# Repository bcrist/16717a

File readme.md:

# 16717A Logic Analyzer Redux

The HP/Agilent 16700A/B and 16702A/B logic analyzer mainframes were originally released somewhere between 1998 and 1999, and though they have now been obsolete for many years, they can still be useful for hobbyists who need to debug digital circuits with large parallel buses (especially the homebrew CPU community, who build computers from scratch, often using nothing but 7400-series logic and parallel SRAM chips).  These "boat anchors" were the last logic analyzers produced which do not use commodity PC hardware or run Windows; instead they run HP's unix variant (HP-UX) on a 150MHz PA-RISC processor.  All the operating system and analysis software is still available, and can be run from a SCSI hard drive emulator like SCSI2SD or ZuluSCSI.  And since it is just an X-windows application, you can run an X server on a modern machine with a high resolution monitor and then view the analysis software on that instead of being limited to the built-in 1024x768 LCD.

The actual triggering, sampling, and storage of waveform data is done on up to five modules.  HP/Agilent produced a variety of these, but the ones most commonly found today are:
* 16710A, 16711A, 16712A: up to 128k sample depth, 104 channels (max. 208 with 2 modules), 100MHz state analysis, 500MHz timing analysis
* 16715A, 16716A, 16717A: up to 4M sample depth, 68 channels (max. 340 with 5 modules), 333MHz state analysis, 2GHz timing analysis (except 16715A)

There's only two different PCBs used for these and the lower model numbers are effectively just software limited to a lower memory depth and can be "upgraded" by adding or removing a resistor (apart from the 16715A which lacks all the timing zoom chips).

All the 167xxA modules had plastic sliders on the bottom to prevent damage to any components on that side if not installed carefully.  Unfortunately, these rails were attached with a foam/rubber adhesive that over time either becomes corrosive, or absorbs water from the air which then becomes corrosive.  This has been documented extensively on the [EEVblog forums](https://www.eevblog.com/forum/repair/series-defect-on-agilent-167xx-boards/).  It seems this corrosion begins to appear pretty reliably around 5 years after the board was made.  As of 2025, any board which has not already had the rails removed is almost guaranteed to no longer be fully functional.  Depending on the damage, it may still be possible to repair, but if any corrosion managed to work its way into a via connecting to one of the internal signal layers, it will likely be unfixable.  I have a handful of 16717A boards like this, and multi-layer PCBs have become surprisingly affordable in recent years, so I decided to desolder all the components from one and sand down the PCB layer by layer to reverse engineer it.  You can find the scans from this in the [scans](./scans/) directory.

# Reference Design
In the [original](./original/) directory you can find my reverse-engineered version of the 16717A that is as close to the original board design as I could make it based on my scans.  Due to distortion, there may be some errors in component and trace placement, however it includes all test points from the original and should be useful when debugging failed 16717A boards.  Unfortunately there are a number of signals that I can't confidently guess at their purpose, so I just named them things like `CTRL1` etc.

# Redux Design
I wasn't happy with a number of things about the original design, so I decided to create a modified version that I think should be more reliable, and if you're going to have these boards made, it's the one I would suggest.  This version is pictured above, and the details can be found in the [redux](./redux) directory.  As of this writing, ordering a set of 5 PCBs from JLCPCB will cost between $260 - $310 depending on solder mask color and shipping selections.

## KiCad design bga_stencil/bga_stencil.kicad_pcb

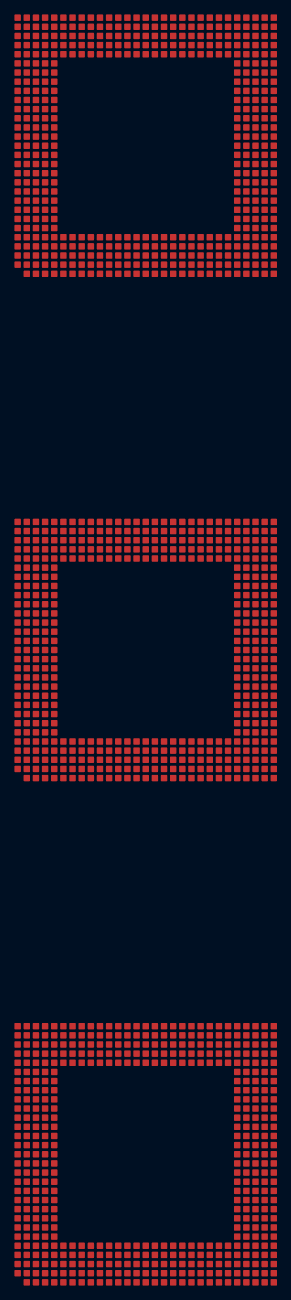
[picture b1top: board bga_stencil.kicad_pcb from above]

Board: 2 copper layers, 3 parts (0 on the bottom side), 2 nets, no tracks yet.

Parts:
U1, U2, U3: 1821-3936; BGA-479_40.5mm_P1.27mm_Stencil

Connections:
+3.3V: U1.A3 (+3.3V), U1.A5 (+3.3V), U1.A10 (+3.3V), U1.A11 (+3.3V), U1.A14 (+3.3V), U1.A16 (+3.3V), U1.A19 (+3.3V), U1.A20 (+3.3V), U1.A27 (+3.3V), U1.A29 (+3.3V), U1.AA1 (+3.3V), U1.AB3 (+3.3V), U1.AB29 (+3.3V), U1.AC1 (+3.3V), U1.AC3 (+3.3V), U1.AC5 (+3.3V), U1.AC10 (+3.3V), U1.AC11 (+3.3V), U1.AC14 (+3.3V), U1.AC16 (+3.3V), U1.AC19 (+3.3V), U1.AC20 (+3.3V), U1.AC27 (+3.3V), U1.AC29 (+3.3V), U1.B2 (+3.3V), U1.C1 (+3.3V), U1.C29 (+3.3V), U1.J1 (+3.3V), U1.J29 (+3.3V), U1.K1 (+3.3V), U1.K29 (+3.3V), U1.N1 (+3.3V), U1.N29 (+3.3V), U1.P1 (+3.3V), U1.R29 (+3.3V), U1.S1 (+3.3V), U1.S29 (+3.3V), U1.T1 (+3.3V), U1.T29 (+3.3V), U1.W29 (+3.3V), U2.A3 (+3.3V), U2.A5 (+3.3V), U2.A10 (+3.3V), U2.A11 (+3.3V), U2.A14 (+3.3V), U2.A16 (+3.3V), U2.A19 (+3.3V), U2.A20 (+3.3V), U2.A27 (+3.3V), U2.A29 (+3.3V), U2.AA1 (+3.3V), U2.AB3 (+3.3V), U2.AB29 (+3.3V), U2.AC1 (+3.3V), U2.AC3 (+3.3V), U2.AC5 (+3.3V), U2.AC10 (+3.3V), U2.AC11 (+3.3V), U2.AC14 (+3.3V), U2.AC16 (+3.3V), U2.AC19 (+3.3V), U2.AC20 (+3.3V), U2.AC27 (+3.3V), U2.AC29 (+3.3V), U2.B2 (+3.3V), U2.C1 (+3.3V), U2.C29 (+3.3V), U2.J1 (+3.3V), U2.J29 (+3.3V), U2.K1 (+3.3V), U2.K29 (+3.3V), U2.N1 (+3.3V), U2.N29 (+3.3V), U2.P1 (+3.3V), U2.R29 (+3.3V), U2.S1 (+3.3V), U2.S29 (+3.3V), U2.T1 (+3.3V), U2.T29 (+3.3V), U2.W29 (+3.3V), U3.A3 (+3.3V), U3.A5 (+3.3V), U3.A10 (+3.3V), U3.A11 (+3.3V), U3.A14 (+3.3V), U3.A16 (+3.3V), U3.A19 (+3.3V), U3.A20 (+3.3V), U3.A27 (+3.3V), U3.A29 (+3.3V), U3.AA1 (+3.3V), U3.AB3 (+3.3V), U3.AB29 (+3.3V), U3.AC1 (+3.3V), U3.AC3 (+3.3V), U3.AC5 (+3.3V), U3.AC10 (+3.3V), U3.AC11 (+3.3V), U3.AC14 (+3.3V), U3.AC16 (+3.3V), U3.AC19 (+3.3V), U3.AC20 (+3.3V), U3.AC27 (+3.3V), U3.AC29 (+3.3V), U3.B2 (+3.3V), U3.C1 (+3.3V), U3.C29 (+3.3V), U3.J1 (+3.3V), U3.J29 (+3.3V), U3.K1 (+3.3V), U3.K29 (+3.3V), U3.N1 (+3.3V), U3.N29 (+3.3V), U3.P1 (+3.3V), U3.R29 (+3.3V), U3.S1 (+3.3V), U3.S29 (+3.3V), U3.T1 (+3.3V), U3.T29 (+3.3V), U3.W29 (+3.3V)
GND: U1.A2 (GND), U1.A4 (GND), U1.A7 (GND), U1.A8 (GND), U1.A9 (GND), U1.A12 (GND), U1.A15 (GND), U1.A18 (GND), U1.A21 (GND), U1.A22 (GND), U1.A23 (GND), U1.A25 (GND), U1.A26 (GND), U1.A28 (GND), U1.AA29 (GND), U1.AB1 (GND), U1.AB2 (GND), U1.AB28 (GND), U1.AC2 (GND), U1.AC4 (GND), U1.AC7 (GND), U1.AC8 (GND), U1.AC9 (GND), U1.AC12 (GND), U1.AC15 (GND), U1.AC18 (GND), U1.AC21 (GND), U1.AC22 (GND), U1.AC23 (GND), U1.AC25 (GND), U1.AC26 (GND), U1.AC28 (GND), U1.B1 (GND), U1.B29 (GND), U1.D1 (GND), U1.D29 (GND), U1.E1 (GND), U1.E29 (GND), U1.G1 (GND), U1.G29 (GND), U1.H1 (GND), U1.H29 (GND), U1.I1 (GND), U1.I29 (GND), U1.L1 (GND), U1.L29 (GND), U1.O1 (GND), U1.O29 (GND), U1.P29 (GND), U1.R1 (GND), U1.U1 (GND), U1.U29 (GND), U1.V1 (GND), U1.V29 (GND), U1.W1 (GND), U1.Y1 (GND), U1.Y29 (GND), U1.Z1 (GND), U1.Z29 (GND), U2.A2 (GND), U2.A4 (GND), U2.A7 (GND), U2.A8 (GND), U2.A9 (GND), U2.A12 (GND), U2.A15 (GND), U2.A18 (GND), U2.A21 (GND), U2.A22 (GND), U2.A23 (GND), U2.A25 (GND), U2.A26 (GND), U2.A28 (GND), U2.AA29 (GND), U2.AB1 (GND), U2.AB2 (GND), U2.AB28 (GND), U2.AC2 (GND), U2.AC4 (GND), U2.AC7 (GND), U2.AC8 (GND), U2.AC9 (GND), U2.AC12 (GND), U2.AC15 (GND), U2.AC18 (GND), U2.AC21 (GND), U2.AC22 (GND), U2.AC23 (GND), U2.AC25 (GND), U2.AC26 (GND), U2.AC28 (GND), U2.B1 (GND), U2.B29 (GND), U2.D1 (GND), U2.D29 (GND), U2.E1 (GND), U2.E29 (GND), U2.G1 (GND), U2.G29 (GND), U2.H1 (GND), U2.H29 (GND), U2.I1 (GND), U2.I29 (GND), U2.L1 (GND), U2.L29 (GND), U2.O1 (GND), U2.O29 (GND), U2.P29 (GND), U2.R1 (GND), U2.U1 (GND), U2.U29 (GND), U2.V1 (GND), U2.V29 (GND), U2.W1 (GND), U2.Y1 (GND), U2.Y29 (GND), U2.Z1 (GND), U2.Z29 (GND), U3.A2 (GND), U3.A4 (GND), U3.A7 (GND), U3.A8 (GND), U3.A9 (GND), U3.A12 (GND), U3.A15 (GND), U3.A18 (GND), U3.A21 (GND), U3.A22 (GND), U3.A23 (GND), U3.A25 (GND), U3.A26 (GND), U3.A28 (GND), U3.AA29 (GND), U3.AB1 (GND), U3.AB2 (GND), U3.AB28 (GND), U3.AC2 (GND), U3.AC4 (GND), U3.AC7 (GND), U3.AC8 (GND), U3.AC9 (GND), U3.AC12 (GND), U3.AC15 (GND), U3.AC18 (GND), U3.AC21 (GND), U3.AC22 (GND), U3.AC23 (GND), U3.AC25 (GND), U3.AC26 (GND), U3.AC28 (GND), U3.B1 (GND), U3.B29 (GND), U3.D1 (GND), U3.D29 (GND), U3.E1 (GND), U3.E29 (GND), U3.G1 (GND), U3.G29 (GND), U3.H1 (GND), U3.H29 (GND), U3.I1 (GND), U3.I29 (GND), U3.L1 (GND), U3.L29 (GND), U3.O1 (GND), U3.O29 (GND), U3.P29 (GND), U3.R1 (GND), U3.U1 (GND), U3.U29 (GND), U3.V1 (GND), U3.V29 (GND), U3.W1 (GND), U3.Y1 (GND), U3.Y29 (GND), U3.Z1 (GND), U3.Z29 (GND)

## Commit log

2024-12-22 setup lfs
2024-12-22 hello, original
2025-01-01 redux work
2025-01-02 replace SOIC resistor arrays
2025-01-05 Rework acquisition ASIC routing
2025-01-06 length matching & rounded tracks
2025-01-07 Clean up FPGA, zoom CS routing
2025-01-18 cleanup DAC caps & routing
2025-01-18 Remove bottom soldermask over BGA vias to facilitate verification of reflow (check for diode drop on I/Os)
2025-01-19 improve routing around fpga
2025-01-19 Allow alternate footprints for FPGA oscillator
2025-01-23 3D models
2025-01-24 documentation
2025-01-24 fix original version ECL routing to ASICs
2025-01-31 clean up routing & add test points on original design
2025-01-31 Fix SY89421V pin 9 held low instead of floating
2025-01-31 remove length matching on ECL comparator outputs
2025-02-05 rev 0 (submitted to jlc)
2025-02-23 rev 1 (submitted to jlc)
2025-03-02 FPGA bringup pv output
2025-03-02 documentation updates
2025-04-04 BGA stencil, ASIC & DRAM bringup notes
2025-04-04 fix typos, remove LFS filters from .gitattributes
2025-04-04 add scans (no LFS)
2025-04-04 add vram/chip numbers to bringup
2025-08-20 readme notes
2025-08-20 add 3d render
2025-08-20 add 3D render to redux/readme.md
2025-08-20 add bringup guide images
2025-08-20 add 3D render for original design
2025-08-24 Finish bringup guide
2025-08-24 Add photo of unknown input inductors
2025-08-24 add ASIC scans to original/readme.md
